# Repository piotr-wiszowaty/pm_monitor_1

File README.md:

pm_monitor_1
============

A particulate matter monitor with BLE and UART interfaces.

The device is based on this [sensor](https://www.dfrobot.com/product-1272.html).
The measured particle concentrations are reported periodically over UART
(FDTI chip based interface) and over BLE. The included server listens for
the incoming BLE reports and stores them in an [InfluxDB](https://www.influxdata.com/) database.

Firmware
--------

The firmware is based on [Mecrisp-Stellaris Forth](http://mecrisp.sourceforge.net/).
Flashing firmware can be done using a communication program (minicom, picocom, etc):

0. flash the Mecrisp-Stellaris Forth core (see note below),
1. send `flash.forth`,
2. send `turnkey.forth`,
3. reset the device.

The microcontroller register and bit field constants can be downloaded from [here](https://github.com/piotr-wiszowaty/comfoh).

Note that to utilize hardware flow control (as in `uc/term.sh`) you need to enable USART2 RTS/CTS
lines in the Mecrisp-Stellaris Forth core.

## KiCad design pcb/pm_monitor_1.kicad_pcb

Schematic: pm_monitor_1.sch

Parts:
C1, C2: 1uF; C_1206_3216Metric_Pad1.42x1.75mm_HandSolder
C3, C9: 10nF; C_0805_2012Metric_Pad1.15x1.40mm_HandSolder
C4, C6, C12, C14: 100nF; C_0805_2012Metric_Pad1.15x1.40mm_HandSolder
C5: 10uF; CP_EIA-3528-21_Kemet-B_Pad1.50x2.35mm_HandSolder
C7, C8: 15pF; C_0805_2012Metric_Pad1.15x1.40mm_HandSolder
C10, C11: 47pF; C_0805_2012Metric_Pad1.15x1.40mm_HandSolder
C13: 330uF; CP_EIA-7343-31_Kemet-D_Pad2.25x2.55mm_HandSolder
D1: PWRLED; LED_0805_2012Metric_Pad1.15x1.40mm_HandSolder
D2, D6: LED; LED_0805_2012Metric_Pad1.15x1.40mm_HandSolder
D3: BTLED; LED_0805_2012Metric_Pad1.15x1.40mm_HandSolder
D4: TXLED; LED_0805_2012Metric_Pad1.15x1.40mm_HandSolder
D5: RXLED; LED_0805_2012Metric_Pad1.15x1.40mm_HandSolder
H1, H2, H3, H4: MountingHole; MountingHole_3.2mm_M3_Pad
J1: USB_B_Micro; USB_Micro-B_Molex_47346-0001
J2: SEN0177; Molex_PicoBlade_53261-0871_1x08-1MP_P1.25mm_Horizontal
J3: SWD; PinHeader_1x06_P2.54mm_Horizontal_HighProfile
L1: 600; L_0805_2012Metric_Pad1.15x1.40mm_HandSolder
R1: 100k; R_0805_2012Metric_Pad1.15x1.40mm_HandSolder
R2: 0; R_0402_1005Metric
R3, R4: 27; R_0805_2012Metric_Pad1.15x1.40mm_HandSolder
R5, R13: 100; R_0805_2012Metric_Pad1.15x1.40mm_HandSolder
R6, R7, R8, R14: 330; R_0805_2012Metric_Pad1.15x1.40mm_HandSolder
R9, R10, R11, R12: 10k; R_0805_2012Metric_Pad1.15x1.40mm_HandSolder
SW1: RESET; SW_SPST_FSMSM
U1: MCP1700-3302E_SOT23; SOT-23
U2: STM32G071KBT; LQFP-32_7x7mm_P0.8mm
U3: RN4871; Microchip_RN4871
U4: FT230XS; SSOP-16_3.9x4.9mm_P0.635mm
Y1: 32.768kHz; Crystal_SMD_Abracon_ABS25-4Pin_8.0x3.8mm

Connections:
+3V3: C2.1, C3.1, C4.1, C5.1, C12.1, D1.2, J3.1, R2.2, R6.1, R7.1, R8.1, R9.1, R10.1, R11.1, R12.1, R13.1, R14.1, U1.2, U2.4 (VDD/VDDA), U3.14, U4.3, U4.11
+5V: C1.1, C13.1, C14.2, J2.8, L1.2, U1.3, U4.12
/BLE_CTS#: U2.23 (PA12_[PA10]), U3.11
/BLE_MODE: U2.16 (PB1), U3.16
/BLE_RST#: U2.17 (PB2), U3.10
/BLE_RTS#: U2.22 (PA11_[PA9]), U3.9
/BLE_RX: U2.19 (PA9), U3.7
/BLE_TX: U2.21 (PA10), U3.8
/FTH_CTS#: R11.2, U2.7 (PA0), U4.2
/FTH_RTS#: R12.2, U2.8 (PA1), U4.6
/FTH_RXD: R9.2, U2.10 (PA3), U4.1
/FTH_TXD: R10.2, U2.9 (PA2), U4.4
/NRST: C6.1, J3.5, SW1.1, U2.6 (PF2-NRST)
/SENSOR_RESET: J2.3, U2.13 (PA6)
/SENSOR_RXD: J2.5
/SENSOR_SET: J2.6, U2.14 (PA7)
/SENSOR_TXD: J2.4, U2.15 (PB0)
/SWCLK: J3.2, U2.25 (PA14-BOOT0)
/SWDIO: J3.4, U2.24 (PA13)
/USBDM: R4.1, U4.9
/USBDP: R3.1, U4.8
/USB_N: C10.1, J1.2, R4.2
/USB_P: C11.1, J1.3, R3.2
/USB_PWREN#: U2.11 (PA4), U4.16
GND: C1.2, C2.2, C3.2, C4.2, C5.2, C6.2, C7.2, C8.2, C9.2, C10.2, C11.2, C12.2, C13.2, C14.1, J1.5, J1.6, J2.7, J3.3, R1.1, R5.2, SW1.2, U1.1, U2.5 (VSS/VSSA), U3.2, U3.13, U4.5, U4.13
unnamed: C7.1, U2.3 (PC15-OSC32_OUT), Y1.4
unnamed: C8.1, U2.2 (PC14-OSC32_IN), Y1.1
unnamed: C9.1, J1.1, L1.1
unnamed: D1.1, R5.1
unnamed: D2.1, U2.20 (PC6)
unnamed: D2.2, R7.2
unnamed: D3.1, U3.12
unnamed: D3.2, R6.2
unnamed: D4.1, U4.14
unnamed: D4.2, R13.2
unnamed: D5.1, U4.7
unnamed: D5.2, R14.2
unnamed: D6.1, U2.18 (PA8)
unnamed: D6.2, R8.2
unnamed: J1.4, R1.2
unnamed: R2.1, U4.10

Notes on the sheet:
(1) Mount to drive 3.3 V rail from the FT230X internal regulator (2) Do not mount when driving 3.3 V rail from FT230X internal regulator
Note (1)
Note (2)
green
red
yellow
blue

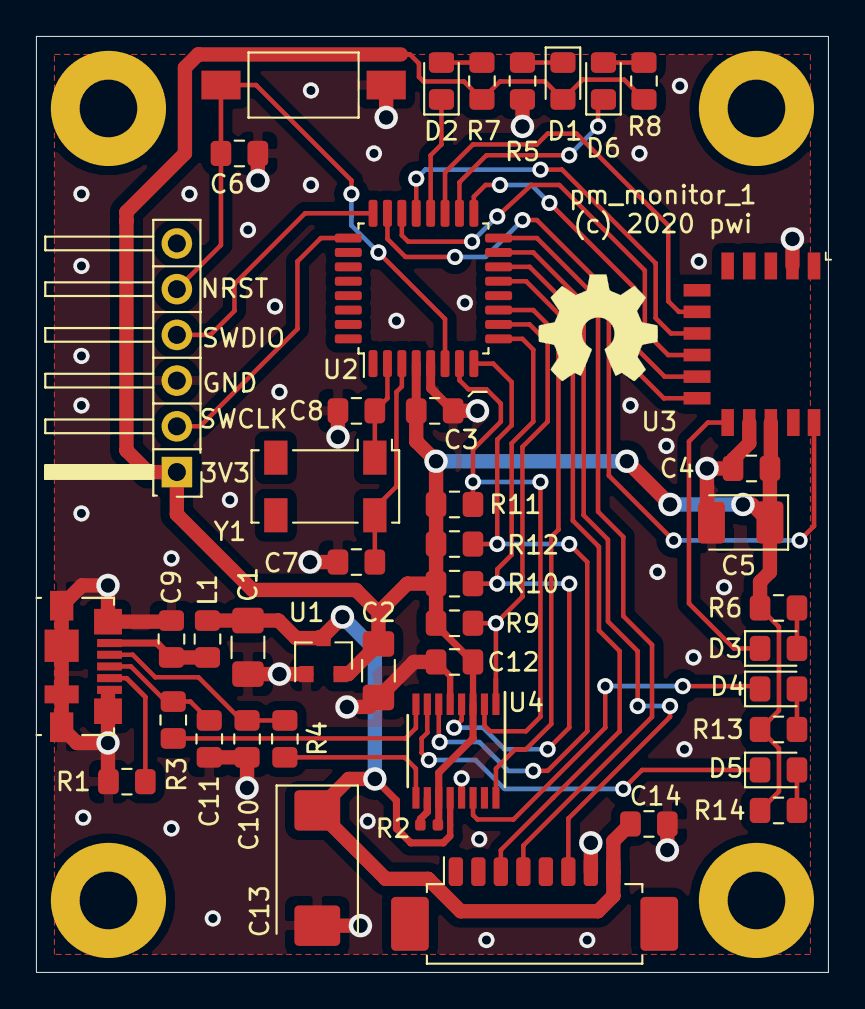
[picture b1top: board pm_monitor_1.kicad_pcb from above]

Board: 2 copper layers, 44.0 x 52.0 mm, 48 parts (0 on the bottom side), 40 nets.

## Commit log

2020-08-22 Add firmware sources
2020-08-22 Add server files
2020-08-22 Add PCB design files
2020-08-22 Add 'enclosure' design files
2020-08-22 Average logged data over measurement batches
2020-08-22 Add Gerber files
2020-08-22 Add a photo of the device
2020-08-22 Add sample plot
2020-09-07 Add UART pass-through functionality
    This is for updating RN4871 firmware with the IsUpdate tool.

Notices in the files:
pcb/pm_monitor_1.kicad_pcb:
(c) 2020 pwi
